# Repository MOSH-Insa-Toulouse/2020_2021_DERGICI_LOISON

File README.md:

# 2020_2021_DERGICI_LOISON

## Plan du Projet Capteur

  - [1. Description](#1-description)
  - [2. Liste des livrables](#2-liste-des-livrables)
  - [3. KiCAD PCB shield - Livrable 1](#3-kicad-pcb-shield---livrable-1)
    - [3.1 Présentation des symboles KiCAD créés](#31-présentation-des-symboles-kicad-créés)
    - [3.2 Rendu 3D du shield designé](#32-rendu-3d-du-shield-designé)
  - [4. Code Arduino - Livrable 2](#4-code-arduino---livrable-2)
  - [5. APK Android interface - Livrable 3](#5-apk-android-interface---livrable-3)
    - [5.1 Notre application: Capteur_Graphite_SDML](#51-notre-application-capteur_graphite_sdml)
    - [5.2 Interface de Capteur_Graphite_SDML](#52-interface-de-capteur_graphite_sdml)
  - [6. Datacheet du capteur - Livrable 4](#6-datacheet-du-capteur---livrable-4)
  - [7. Protocole du banc de test - Livrable 5](#7-protocole-du-banc-de-test---livrable-5)
  - [8. Pistes des améliorations possibles](#8-pistes-des-améliorations-possibles)

## 1. Description 

Ce projet s'inscrit dans l'enseignement de 4éme année génie physique de l'UF "du Banc de Test au Capteur".
Le capteur à réaliser est comparable à une jauge de contrainte à base de graphite.
Le projet comprend:
 - le design et la fabrication d'un PCB shield, 
 - le couplage de la jauge à un circuit analogique, 
 - la communication via un microcontrôleur avec une application Android. 

## 2. Liste des livrables

- [x] KiCAD PCB shield: transimpedance amplifier, BT module, OLED screen
- [x] Code Arduino: mesure jauge contrainte & contrôle communication BT/affichage sur l'OLED
- [x] APK Android interface sur MIT App Inventor: évolution de la valeur de la résistance
- [x] Datasheet du capteur
- [x] Protocole du banc test

Tous les livrales ont été réalisés et sont disponibles sur la plateforme GitHub.

## 3. KiCAD PCB shield - Livrable 1

- PCB simple face designé sur KiCAD :
  - schematics: création d'une biblihothèque dédiée au projet et de nouveaux symboles pour représenter tous les éléments du shield.
  - PCB: routage du circuit transimpédance et des éléments permettant la mesure (module BT, OLED), création des empreintes associées à tous les éléments du shield.
- Accès possible sur GitHub aux fichiers Gerber, à la représentation 3D du shield ainsi qu'aux pdf des pistes

### 3.1 Présentation des symboles KiCAD créés

#### Symbole créé pour le capteur graphite

#### Symbole créé pour l'écran OLED

#### Symbole créé pour le module BlueTooth

#### Symbole créé pour l'ampli LTC1050

### 3.2 Rendu 3D du shield designé

#### Représentation 3D du shield

## 4. Code Arduino - Livrable 2

- Le code Arduino permet la communication avec le téléphone portable (réception et envoi de données sous forme de bit), sur la base d'une machine à états il gère ensuite les différents cas de figure possibles.
Trois cas de figures simples ont été imaginés :
   - début de mesure et d'acquisition (correspond au case action=1): lance la mesure et la sauvegarde des données d'ADC et de résistance, affichage de la valeur de résistance sur l'OLED et l'application, graphe de l'appli suit l'évolution des variations de résistance.
   - fin de mesure et arrêt de l'acquisition (correspond au case action=2): arrête la mesure et met fin à la sauvegarde des données qui sont dès lors accessibles sur le téléphone.
   - default case: gère le cas où action a une valeur anormale (différente de 1 ou 2).
  
- Il traduit la valeur en ADC en valeur de résistance, selon l'équation du circuit établie. Pour éviter les erreurs dues à une mauvaise écriture de l'équation (trop ou pas assez de parenthèses) les déterminants, numérateurs et autres ont été préalablement calculés et une variable leur a été affectée.
- Il gère aussi l'affichage des valeurs de résistance sur l'OLED pendant la mesure, et gère l'arrêt de mesure avec l'affichage de l'écran d'accueil sur l'OLED

## 5. APK Android interface - Livrable 3

### 5.1 Notre application: Capteur_Graphite_SDML
- L'application nommée "Capteur_Graphite_SDML" se connecte par bluetooth au capteur 
- L'état de la connexion s'affiche ainsi que le nom de l'appareil connecté
- Mesure la valeur de la résistance selon la déformation appliquée sur le capteur et l'affiche
- Trace le graphique en temps réel des valeurs d'ADC mesurées (choix de l'ADC et non de la résistance pour le graph. car l'ADC varie moins fortement que la résistance)
- Les données sont sauvegardées sous le nom entré par l'utilisateur et accessibles depuis le téléphone 
- L'arrêt de la mesure est annoncé par l'application (déclenche un message vocal)

### 5.2 Interface de Capteur_Graphite_SDML

## 6. Datacheet du capteur - Livrable 4

- Description du capteur et de l'application associée,
- Dimensions du capteur et exemple d'utilisation,
- Présentation du banc de test,
- Caractéristiques techniques et électriques,
- Caractéristiques (Variation de résistance/Déformation),
- Remarques sur les domaines d'utilisation en déformation.

## 7. Protocole du banc de test - Livrable 5

- On utilise un banc de test demi-circulaire des portions de différents rayons. 
- Les rayons sont compris entre 1 cm et 2.5 cm avec un intervalle de 0.25cm. 
- Chaque rayon est associé à une déformation max applicable au capteur graphite.
- La déformation peut être "interne" ou "externe" en fonction du positionnement du capteur. 
- Une petite fente présente a chaque début de courbure permet de coincer l'extrémité du capteur, ce qui permet de bien épouser la surface du banc de test. 
- Pour une meilleure durée de vie du capteur il est préférable de commencer par les rayons les plus grands (torsion et risque de casse du capteur moins)
- À chaque test, les données (la clock, la valeur de la résistance et la valeur de l'ADC) sont enregistrées dans un fichier texte sur le téléphone (nom typique: "myFile_typeCrayon_rayon.txt").
- Une fois tous les tests effectués selon les différents rayons et selon le type de crayon choisi, les données sont traitées.

## 8. Pistes des améliorations possibles

- Le capteur se détériore trop rapidement et on observe une faible reproductibilité des expériences: il est rare de retrouver les même valeurs de résistance pour un même type de crayon. En effet, tout dépend du nombre de couches de graphène déposées sur le capteur. Ce dépôt reste donc très aléatoire.
- Difficultés à mesurer les valeurs de résistance des crayons du type H: leur résistance est trop faible on ne parvient pas à les détecter.
- Difficultés à mesurer les valeurs de résistances des crayons du type 3B et supérieurs: leur résistance est trop élevée il y a overload.
     
     **=> Il s'agit d'un problème de calibration:**
     - Pour adapter le capteur à tous les types de crayons et maximiser les chances d'obtenir plus facilement des données fiables il faut jouer sur la valeur de R2 dans le circuit transimpédance de notre shield
     
     **=> Nous proposons:**
     - Remplacer la résistance R2 par un potentiomètre, ce qui permet d'accéder à une plus grande gamme de résistances et donc de modifier le gain. Une meilleure modulation du gain permettra de s'adapter aux résistances trop élevées ou trop faibles.
     - Installer un encodeur rotatif et mettre au point sur l'Arduino un menu de présélection permettant d'indiquer avant la mesure le type de crayon qui sera utilisé.
     - Adapter le code Arduino pour permettre l'utilisation de l'encodeur rotatif pour naviguer dans le menu de présélection.
     - Adapter le code Aduino pour mettre au point une phase de calibration du potentiomètre R2 suite au choix du type de crayon.
     - Adapter le code Arduino pour communiquer la nouvelle valeur de R2 à l'application Android et au reste du code Arduino (pour les conversions d'ADC en valeur de résistance).
     - Ajouter un autoscale sur le graphique de l'application Android.

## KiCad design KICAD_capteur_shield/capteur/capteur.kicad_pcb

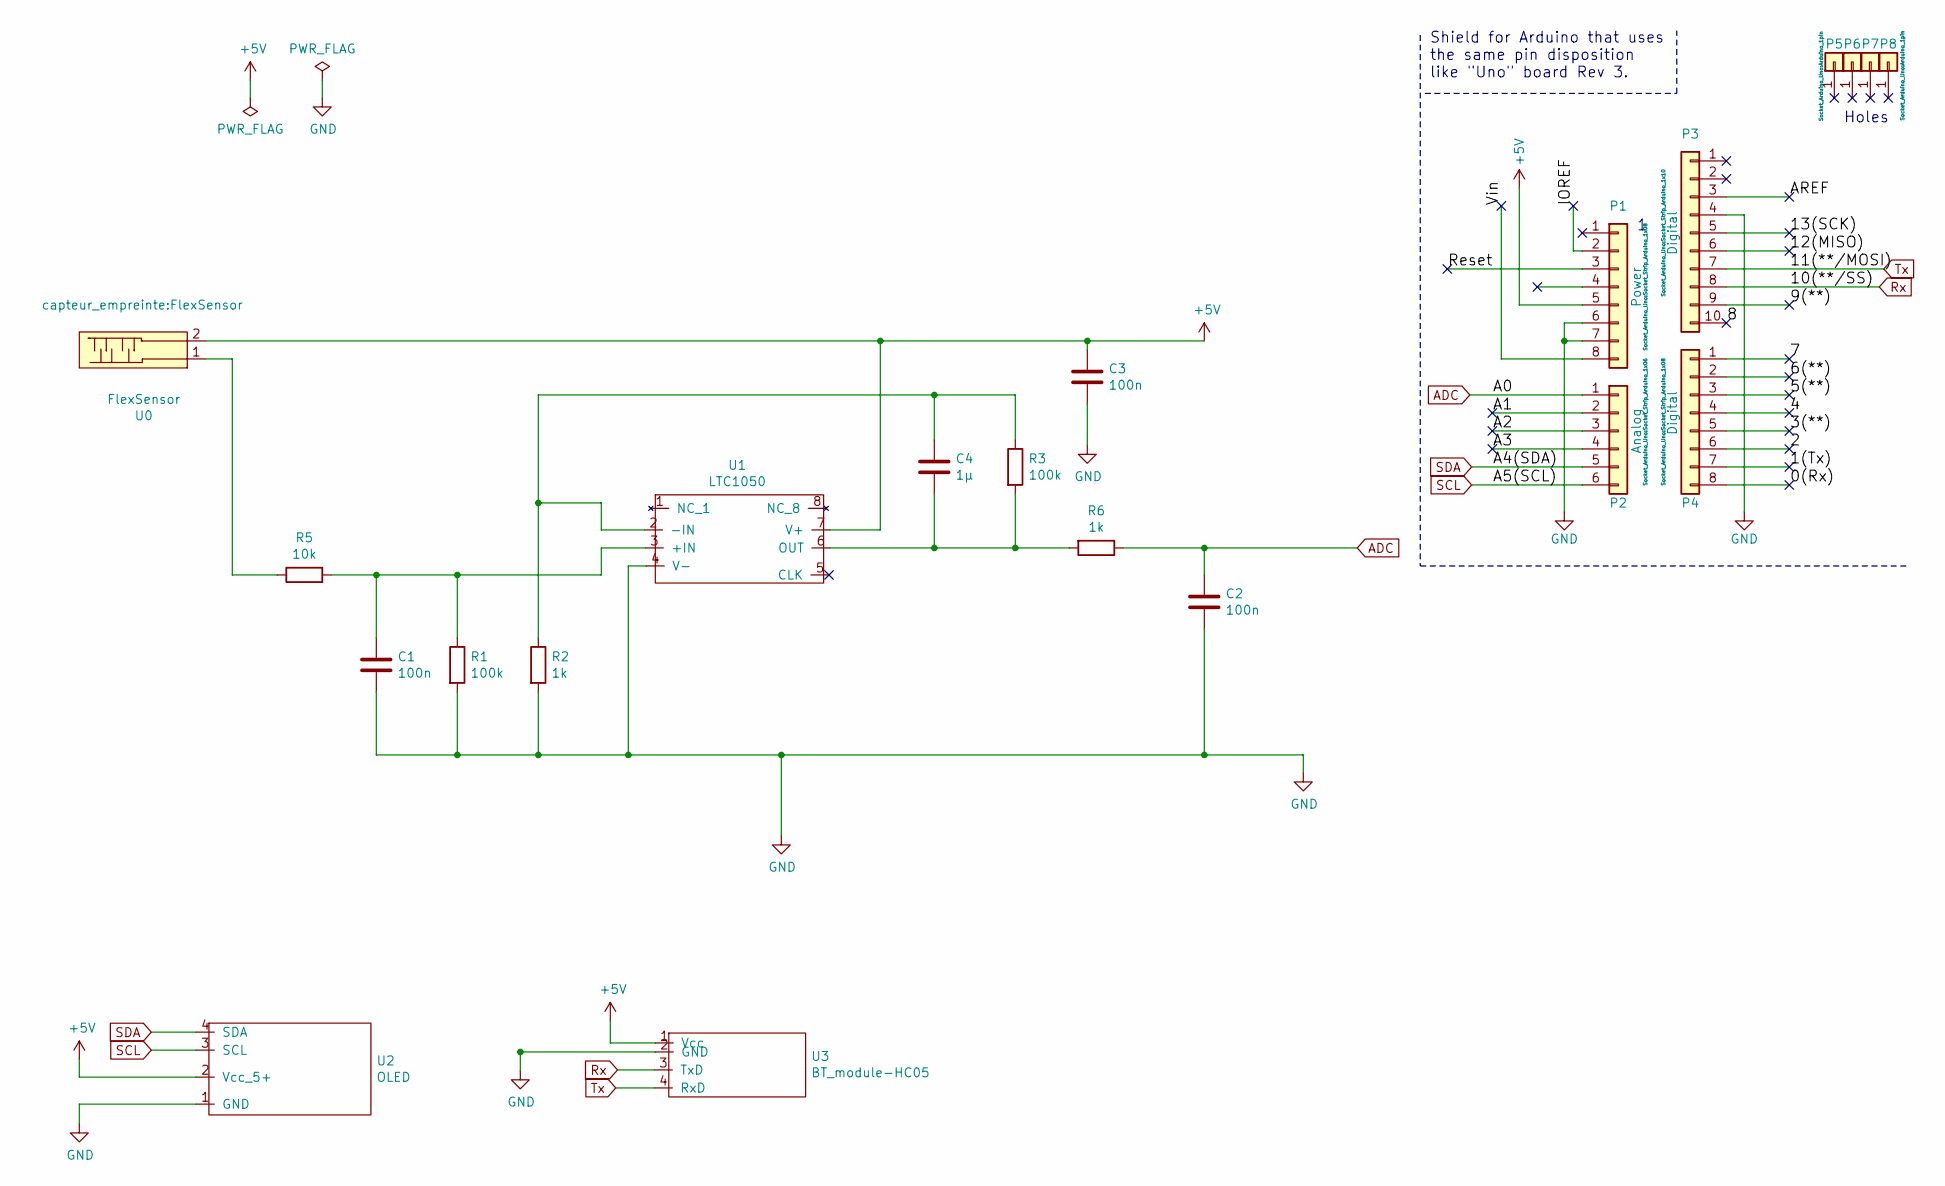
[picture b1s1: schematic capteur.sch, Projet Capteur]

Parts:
C1, C2, C3: 100n; C_Axial_L3.8mm_D2.6mm_P7.50mm_Horizontal
C4: 1µ; C_Rect_L7.0mm_W6.0mm_P5.00mm
P1: Power; Socket_Strip_Arduino_1x08
P2: Analog; Socket_Strip_Arduino_1x06
P3: Digital; Socket_Strip_Arduino_1x10
P4: Digital; Socket_Strip_Arduino_1x08
P5, P6, P7, P8: CONN_01X01; Arduino_1pin
R1, R3: 100k; R_Axial_DIN0204_L3.6mm_D1.6mm_P5.08mm_Horizontal
R2, R6: 1k; R_Axial_DIN0204_L3.6mm_D1.6mm_P5.08mm_Horizontal
R5: 10k; R_Axial_DIN0204_L3.6mm_D1.6mm_P5.08mm_Horizontal
U0: FlexSensor
U1: LTC1050
U2: OLED
U3: BT_module-HC05

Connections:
+5V: C3.2, P1.5, U0.2, U1.7 (V+), U2.2 (Vcc_5+), U3.1 (Vcc)
/0(Rx): P4.8
/1(Tx): P4.7
/2: P4.6
/3(**): P4.5
/4: P4.4
/5(**): P4.3
/6(**): P4.2
/7: P4.1
/8: P3.10
/9(**): P3.9
/12(MISO): P3.6
/13(SCK): P3.5
/A1: P2.2
/A2: P2.3
/A3: P2.4
/AREF: P3.3
/IOREF: P1.2
/Reset: P1.3
/Vin: P1.8
ADC: C2.1, P2.1, R6.1
GND: C1.2, C2.2, C3.1, P1.6, P1.7, P3.4, R1.2, R2.2, U1.4 (V-), U2.1 (GND), U3.2 (GND)
unnamed: C1.1, R1.1, R5.2, U1.3 (+IN)
unnamed: C4.1, R2.1, R3.1, U1.2 (-IN)
unnamed: C4.2, R3.2, R6.2, U1.6 (OUT)
unnamed: R5.1, U0.1
Rx: P3.8, U3.3 (TxD)
SCL: P2.6, U2.3 (SCL)
SDA: P2.5, U2.4 (SDA)
Tx: P3.7, U3.4 (RxD)

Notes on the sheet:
Holes
Shield for Arduino that uses the same pin disposition like "Uno" board Rev 3.

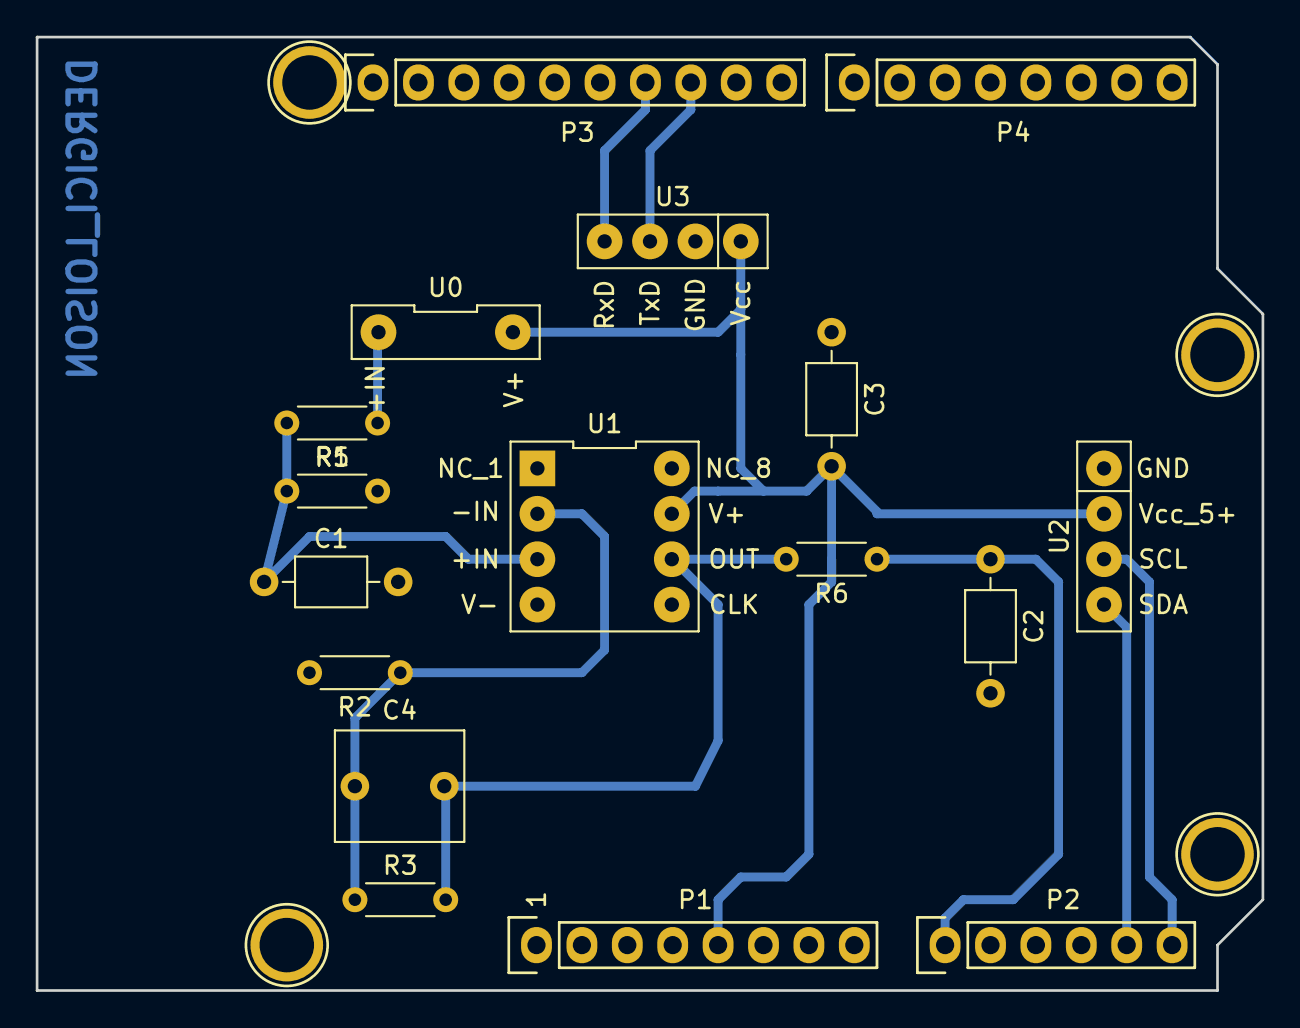
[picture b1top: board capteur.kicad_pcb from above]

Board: 2 copper layers, 68.6 x 53.3 mm, 21 parts (0 on the bottom side), 11 nets.

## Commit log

2021-02-05 test
2021-04-01 MàJ_README_#01/04
2021-04-01 commit_folderKiCAD
2021-04-09 maj_fichiersKiCAD
2021-04-09 maj_KiCAD
2021-04-12 MaJ_datasheet+arduino+app
2021-04-12 MaJ_README
2021-04-12 MàJ_PlanREADME
2021-04-12 MàJ_README_Images
2021-04-12 MàJ_Images
2021-04-19 MàJ_README
2021-05-05 MàJ_Datasheet
2021-05-05 MàJ_code_arduino_commentaires
